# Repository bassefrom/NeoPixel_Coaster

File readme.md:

# NeoPixel Coaster
#
# The NeoPixel coaster is a battery driven coaster that light up using NeoPixels. 
# The NeoPixels are driven with an attiny85. 
# The colors of the NeoPixels are temperature dependent and the attiny85 is connected to a thermistor to calculate the appropriate RGB values for.
#
# Programming the attiny85:
#
# Program the Arduino Uno with Arduino as ISP example program
#
# Add support for attiny85 in Arduino IDE:
# Go to preferences in Arduino IDE.
# Add this line to Additional Boards Manager URLs: https://raw.githubusercontent.com/damellis/attiny/ide-1.6.x-boards-manager/package_damellis_attiny_index.json
# Under Tools, select ATtiny25/45/85 board
# Select ATtiny85 as Processor
# Select Internal 8MHz clock
#
# Connect Arduino pin 13 (SCK) to attiny85 pin 7
# Connect Arduino pin 12 (MISO) to attiny85 pin 6
# Connect Arduino pin 11 (MOSI) to attiny85 pin 5
# Connect Arduino pin 10 (RESET) to attiny85 pin 1
# Connect Arduino 5V to attiny85 pin 8
# Connect Arduino GND to attiny85 pin 4
#
# Burn Arduino bootloader to attiny85
# Program the attiny85 from Arduino IDE
#
#
# AVRDUDE programming to be implemented (not supported as of now):
# How to use avrdude for programming HEX-files to the attiny85 using Arduino Uno as ISP:
# Connect the attiny85 in the same way you connect it when programming using the Arduino IDE.
# attiny85 has name t85 in avrdude. Use the following line to verify the attiny85 is connected properly:
# avrdude -c avrisp -b 19200 -p t85 -P COMX -n
# Set 8MHz internal oscillator using these fuse bits: 0xE2 and 0xD9 with the followign line:
# avrdude -c avrisp -b 19200 -p t85 -P COMX -U lfuse:w:0xE2:m -U hfuse:w:0xD9:m
# Program the attiny85 using this line:
# avrdude -P COM1 -b 19200 -c avrisp -p t85 -u -U flash:w:"{HEX-file directory here}\file.hex":i
#
# It can be done using a single line as well:
# avrdude -P COM1 -b 19200 -c avrisp -p t85 -u -U efuse:w:0xFF:m -U lfuse:w:0xE2:m -U hfuse:w:0xD9:m -U flash:w:"{HEX-file directory here}\file.hex":i
#
# Example: avrdude -P COM1 -b 19200 -c avrisp -p t85 -u -U efuse:w:0xFF:m -U lfuse:w:0xE2:m -U hfuse:w:0xD9:m -U flash:w:"C:\Users\Basse\Documents\KiCad\NeoPixel_Coaster\Software\ATTiny85_NeoPixel\ATTiny85_NeoPixel.ino.hex":i

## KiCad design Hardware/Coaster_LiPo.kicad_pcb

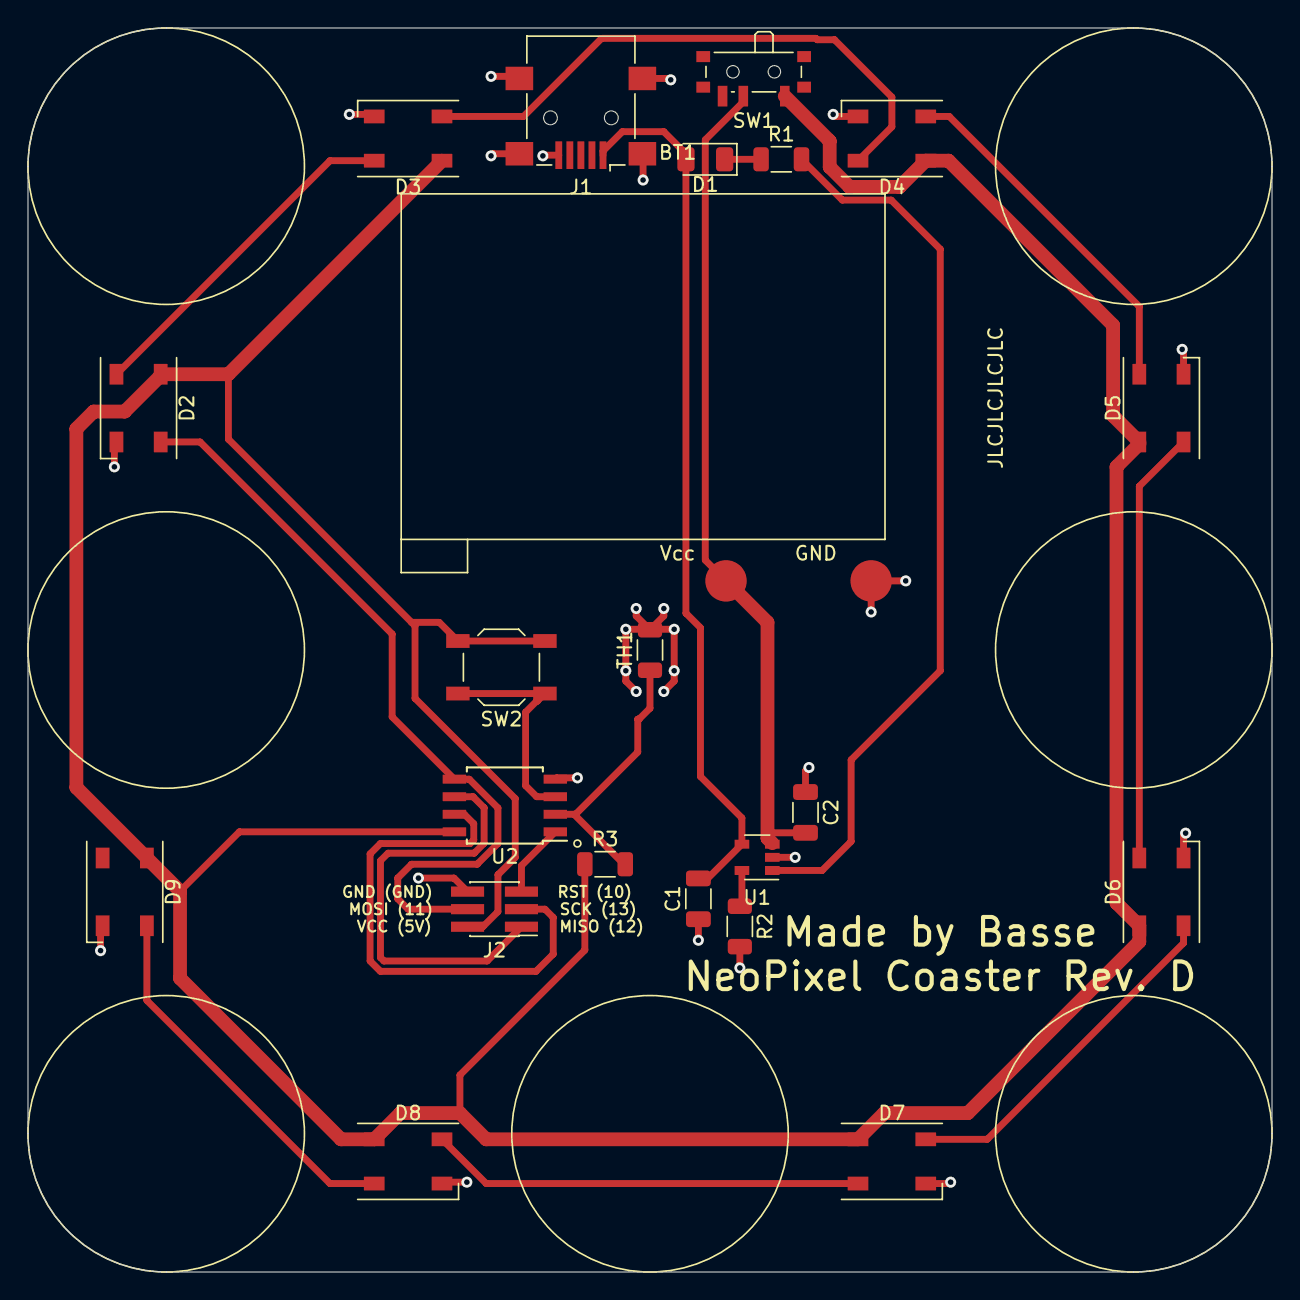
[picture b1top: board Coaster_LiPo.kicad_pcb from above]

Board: 2 copper layers, 90.0 x 90.0 mm, 22 parts (0 on the bottom side), 20 nets.

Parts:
BT1: Battery_Cell; Batteri LiPo 3.7V 400mAh
C1, C2: 4.7u; C_1206_3216Metric
D1: LED; LED_1206_3216Metric
D2, D3, D4, D5, D6, D7, D8, D9: SK6812; LED_SK6812_PLCC4_5.0x5.0mm_P3.2mm
J1: USB_B_Mini; USB_Mini-B_Lumberg_2486_01_Horizontal
J2: Conn_02x03_Odd_Even; PinHeader_2x03_P1.27mm_Vertical_SMD
R1: 2.2k; R_1206_3216Metric
R2: 4.7k; R_1206_3216Metric
R3: 100k; R_1206_3216Metric
SW1: SW_SPDT; SW_SPDT_PCM12
SW2: SW_Push; SW_SPST_TL3342
TH1: Thermistor; R_1206_3216Metric
U1: MCP73831-2-OT; SOT-23-5
U2: ATtiny85-20SU; SOIJ-8_5.3x5.3mm_P1.27mm

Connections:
GND: BT1.2, C1.1, C2.1, D2.1, D3.1, D4.1, D5.1, D6.1, D7.1, D8.1, D9.1, J1.5, J1.6, J2.6, R2.2, TH1.2, U1.2, U2.4
MISO: J2.1, U2.6
MOSI: D2.2, J2.4, U2.5
unnamed: BT1.1, C2.2, SW1.2, U1.3
unnamed: C1.2, D1.2, J1.1, U1.4
unnamed: D1.1, R1.1
unnamed: D2.4, D3.2
unnamed: D3.4, D4.2
unnamed: D4.4, D5.2
unnamed: D5.4, D6.2
unnamed: D6.4, D7.2
unnamed: D7.4, D8.2
unnamed: D8.4, D9.2
unnamed: R1.2, U1.1
unnamed: R2.1, U1.5
unnamed: SW2.1, U2.3
Reset: J2.5, U2.1
SCK: J2.3, U2.7
SensOut: R3.2, TH1.1, U2.2
Vcc: D2.3, D3.3, D4.3, D5.3, D6.3, D7.3, D8.3, D9.3, J2.2, R3.1, SW1.1, SW2.2, U2.8

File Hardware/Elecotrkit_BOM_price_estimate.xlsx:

Id | Designator | Package | Quantity | Designation | Supplier and ref | Styckpris | 10st styckpris | Totalt pris | Totalt pris vid 5st | Enhetspris vid 10st
1 | BT1 | LiPo Battery 150mAh | 1 | Battery_Cell | https://www.electrokit.com/produkt/batteri-lipo-3-7v-400mah-2/ | 75 | 67.5 | 75 | 375 | 67.5
2 | J1 | USB_Mini-B_No_Holes | 1 | USB_B_Mini | https://www.electrokit.com/produkt/usb-mini-b-smd/ | 8.24 | 7.42 | 8.24 | 41.2 | 7.42
3 | C1,C2 | C_1206_3216Metric | 2 | 4.7u | https://www.electrokit.com/produkt/kondensator-1206-x7r-4-7u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 | 4 | 4 | 8 | 40 | 8
4 | D1 | D_1206_3216Metric | 1 | LED | https://www.electrokit.com/produkt/led-orange-1206-100-mcd-klar/ | 2.4500000000000002 | 2.21 | 2.4500000000000002 | 12.25 | 2.21
5 | D2,D3,D4,D5 | WS2812_2020_SMD | 4 | WS2812B | https://www.electrokit.com/produkt/led-smd5050-rgb-adresserb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 | 5.5 | 4.68 | 22 | 110 | 18.72
6 | J2 | PinHeader_2x03_P1.27mm_Vertical_SMD | 1 | Conn_02x03_Odd_Even | https://www.electrokit.com/produkt/stiftlist-1-27mm-2x40p-smd/ or https://www.e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 | 1.5 | 1.5 | 1.5 | 7.5 | 1.5
7 | R1 | R_1206_3216Metric | 1 | 1k | https://www.electrokit.com/produkt/motstand-1kohm-0-25w-smd-1206/ | 0.35 | 0.35 | 0.35 | 1.75 | 0.35
8 | R2 | R_1206_3216Metric | 1 | 4.7k | https://www.electrokit.com/produkt/motstand-4-7kohm-0-25w-smd-1206/ | 0.35 | 0.35 | 0.35 | 1.75 | 0.35
9 | R3 | R_1206_3216Metric | 1 | 100k | https://www.electrokit.com/produkt/motstand-100kohm-0-25w-smd-1206/ | 0.35 | 0.35 | 0.35 | 1.75 | 0.35
10 | S1 | Skjutomkopplare 2-pol on-on-on pcb | 1 | EG1218 | https://www.electrokit.com/produkt/skjutomkopplare-mini-1-po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 | 9 | 8.1 | 9 | 45 | 8.1
11 | TH1 | R_1206_3216Metric | 1 | Thermistor | https://www.electrokit.com/produkt/ntc-100kohm-smd-1206/ | 4 | 3.6 | 4 | 20 | 3.6
12 | U1 | SOT-23-5 | 1 | MCP73831-2-OT | https://www.electrokit.com/produkt/mcp73831t-2aci-ot-sot-23-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 | 6.63 | 5.97 | 6.63 | 33.15 | 5.97
13 | U2 | SOIJ-8_5.3x5.3mm_P1.27mm | 1 | ATtiny85-20SU | https://www.electrokit.com/produkt/attiny85-20su-so-8-8-bit-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 | 29 | 26.1 | 29 | 145 | 26.1
 |  |  |  |  |  |  | Totalt | 166.86999999999998 | 834.35 | 150.16999999999996

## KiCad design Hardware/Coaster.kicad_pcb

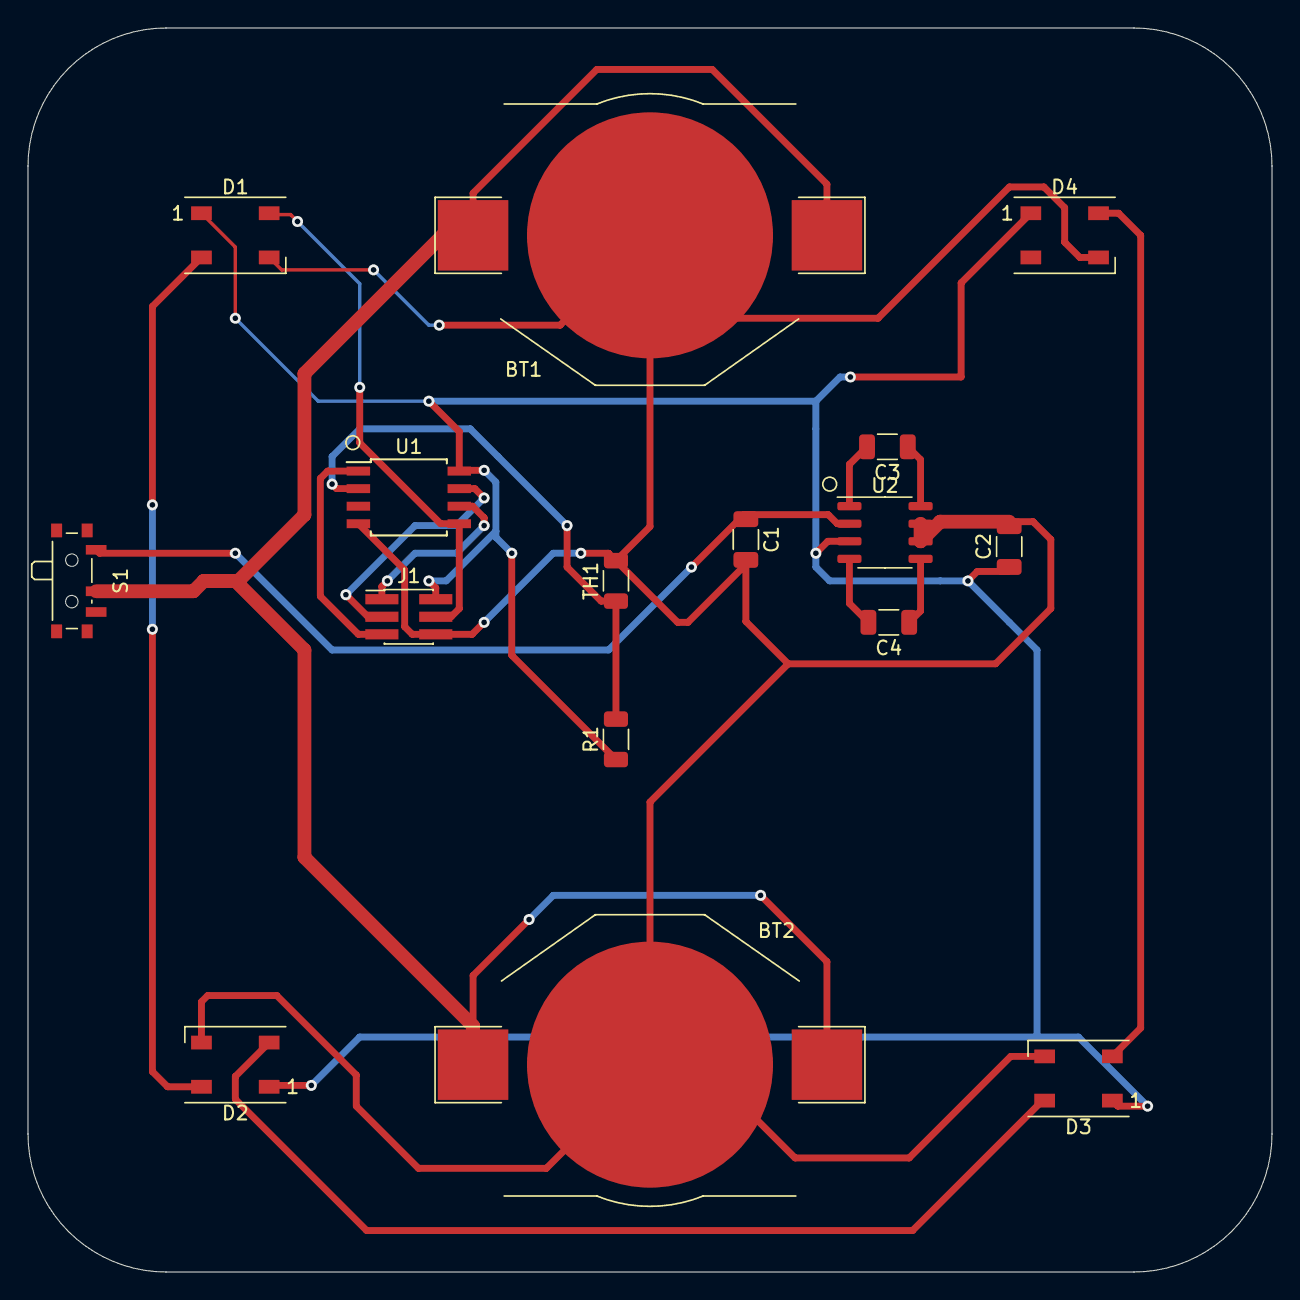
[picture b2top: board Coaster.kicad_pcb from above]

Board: 2 copper layers, 90.0 x 90.0 mm, 16 parts (0 on the bottom side), 16 nets.

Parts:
BT1, BT2: Battery_Cell_Holder_SMD; BatteryHolder_Keystone_3002_1x2032
C1, C2: 10u; C_1206_3216Metric
C3, C4: 0.22u; C_1206_3216Metric
D1, D2, D3, D4: WS2812B; LED_WS2812B_PLCC4_5.0x5.0mm_P3.2mm
J1: Conn_02x03_Odd_Even; PinHeader_2x03_P1.27mm_Vertical_SMD
R1: 100k; R_1206_3216Metric
S1: EG1218; SW_SPDT_PCM12
TH1: Thermistor_NTC; R_1206_3216Metric
U1: ATtiny85-20SU; SOIJ-8_5.3x5.3mm_P1.27mm
U2: MAX619_MyOwn; SO-8_3.9x4.9mm_P1.27mm

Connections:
3V: C1.1, S1.1, U2.2
5V: C2.1, D1.1, D2.1, D3.1, D4.1, J1.2, R1.1, U1.8, U2.3
GND: BT1.2, BT2.2, C1.2, C2.2, D1.3, D2.3, D3.3, D4.3, J1.6, TH1.2, U1.4, U2.6, U2.7
MISO: J1.1, U1.6
MOSI: D1.4, J1.4, U1.5
unnamed: BT1.1, BT2.1, S1.2
unnamed: C3.1, U2.8
unnamed: C3.2, U2.1
unnamed: C4.1, U2.5
unnamed: C4.2, U2.4
unnamed: D1.2, D2.4
unnamed: D2.2, D3.4
unnamed: D3.2, D4.4
RESET: J1.5, U1.1
SCK: J1.3, U1.7
SensOut: R1.2, TH1.1, U1.2

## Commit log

2021-02-05 Changed LEDs to 5050 and switch to standard SPDT
2021-02-05 Replaced CR2032 batteries with LiPo. Boost converted changed to charge IC. Silk screen for rubber feet added
2021-02-05 Updated the readme
2021-02-05 Added Attiny85 Arduino code
2021-02-05 Renamed code file and capped LED intensity to 25 for each color
2021-02-05 Changed a comment in the code
2021-02-05 Test permissions commit
2021-02-05 DigiKey components added
2021-03-02 Updated Readme and minor tweaks after first prototype build
2021-03-05 Updated readme for newLayout version
2021-03-06 Added graphics, rearranged components, added 4 more neopixels
2021-04-17 Added push button to cycle through LED modes
2021-04-18 Moved a via and limited logo
2021-04-18 Removed old gerbers
